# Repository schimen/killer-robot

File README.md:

# Killer robot

This repository contains all code and circuit for the robot **Rupert**, competing in [RoboWars](https://omegav.no/robotkrig) at [Omega Verksted](https://omegav.no/).

More information about Rupert and his history can be found in [history.md](./history.md).

## Projects

This repository consists of differenct projects that have different tasks in controlling the robot.
The different projects are:
- [Robot brain](./firmware/rupert-brain/): Firmware running on Rupert, receives commands and controls motors.
- [Robot pcb](./robot-pcb/): Printed circuit board supposed to control the robot. The robot brain runs on this hardware.
- [Robot control center](./control-center/): Python GUI program that controls the robot via commands.
- [Transmitter](./firmware/transmitter): Firmware for command transmitter, communicating with the control center via USB and the robot via radio.
This transmitter is deprecated, all communication with Rupert uses BLE via the "Robot control center".

## Zephyr guide

The firmware for Rupert is mainly developed in [Zephyr RTOS](https://www.zephyrproject.org/) and the SDK for Zephyr must be installed to build and upload firmware to the robot and the transmitter.
Zephyr is well documented and the latest documentation can be found [here](https://docs.zephyrproject.org/latest/index.html).

To install and get started with Zephyr, please follow [this guide](https://docs.zephyrproject.org/latest/develop/getting_started/index.html).
To install Zephyr in this project, make sure west and other dependencies from the guide is installed, and run `west update` from this repositories root folder. This will download Zephyr and relevant modules.
After installing and becoming familiar with the framework, you can install dependencies used by our hardware:
- Install ESP32 dependencies with `west espressif install`. Alternatively, follow [this guide](https://www.zephyrproject.org/zephyr-rtos-on-esp32/).

The Rupert firmware can now for example be built by the command `west build -b rupert_pcb firmware/rupert-brain` and then flashed with the command `west flash`.

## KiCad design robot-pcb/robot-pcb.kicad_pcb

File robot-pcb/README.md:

# Robot PCB

This is the PCB that controls Rupert.
It consists of a ESP32 microcontroller that communicates over bluetooth.
Motors are controlled via motor-driver and via pwm outputs.

Schematic:

PCB 3d render:

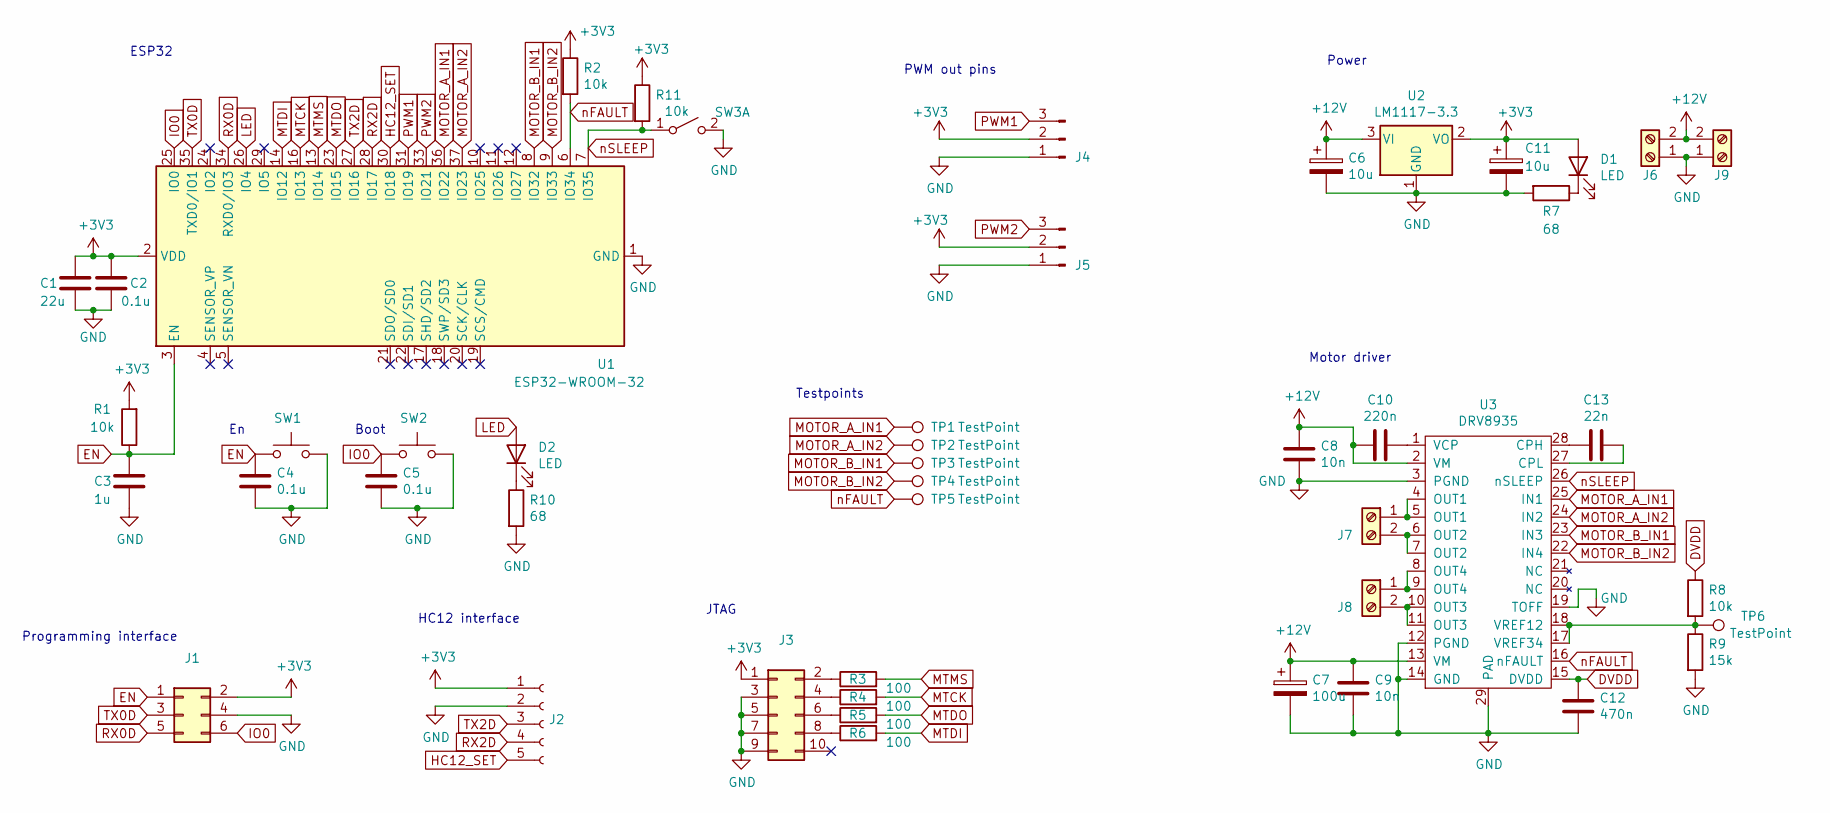
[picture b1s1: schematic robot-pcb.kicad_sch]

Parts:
C1: 22u; C_0603_1608Metric_Pad1.08x0.95mm_HandSolder
C2, C4, C5: 0.1u; C_0603_1608Metric_Pad1.08x0.95mm_HandSolder
C3: 1u; C_0603_1608Metric_Pad1.08x0.95mm_HandSolder
C6, C11: 10u; C_1206_3216Metric_Pad1.33x1.80mm_HandSolder
C7: 100u; CP_Elec_6.3x7.7
C8, C9: 10n; C_0603_1608Metric_Pad1.08x0.95mm_HandSolder
C10: 220n; C_0603_1608Metric_Pad1.08x0.95mm_HandSolder
C12: 470n; C_0603_1608Metric_Pad1.08x0.95mm_HandSolder
C13: 22n; C_0603_1608Metric_Pad1.08x0.95mm_HandSolder
D1, D2: LED; LED_0603_1608Metric_Pad1.05x0.95mm_HandSolder
J1: Conn_02x03_Odd_Even; PinHeader_2x03_P1.27mm_Vertical_SMD
J2: Conn_01x05_Female; PinSocket_1x05_P2.54mm_Vertical
J3: Conn_02x05_Odd_Even; PinHeader_2x05_P1.27mm_Vertical_SMD
J4, J5: Conn_01x03_Male; PinSocket_1x03_P2.54mm_Vertical
J6, J7, J8, J9: Screw_Terminal_01x02; TerminalBlock_bornier-2_P5.08mm
R1, R2, R8, R11: 10k; R_0603_1608Metric_Pad0.98x0.95mm_HandSolder
R3, R4, R5, R6: 100; R_0603_1608Metric_Pad0.98x0.95mm_HandSolder
R7, R10: 68; R_0603_1608Metric_Pad0.98x0.95mm_HandSolder
R9: 15k; R_0603_1608Metric_Pad0.98x0.95mm_HandSolder
SW1, SW2: SW_Push; wurth_tactile_sw
SW3: SW_DPST_x2; PinHeader_1x02_P2.54mm_Vertical
TP1, TP2, TP3, TP4, TP5, TP6: TestPoint; TestPoint_Keystone_5000-5004_Miniature
U1: ESP32-WROOM-32
U2: LM1117-3.3; SOT-223
U3: DRV8935; HTSSOP-28-1EP_4.4x9.7mm_P0.65mm_EP2.85x5.4mm

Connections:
+3V3: C1.1, C2.1, C11.1, D1.2 (A), J1.2, J2.1, J3.1, J4.2, J5.2, R1.2, R2.1, R11.1, U1.2 (VDD), U2.2 (VO), U2.4
+12V: C6.1, C7.1, C8.1, C9.1, C10.2, J6.2, J9.2, U2.3 (VI), U3.2 (VM), U3.13 (VM)
DVDD: C12.1, R8.1, U3.15 (DVDD)
EN: C3.1, C4.1, J1.1, R1.1, SW1.2, U1.3 (EN)
GND: C1.2, C2.2, C3.2, C4.2, C5.2, C6.2, C7.2, C8.2, C9.2, C11.2, C12.2, J1.4, J2.2, J3.3, J3.5, J3.7, J3.9, J4.1, J5.1, J6.1, J9.1, R7.2, R9.2, R10.2, SW1.1, SW2.2, SW3.2 (B), U1.1 (GND), U1.15 (GND), U1.38 (GND), U1.39 (GND), U2.1 (GND), U3.3 (PGND), U3.12 (PGND), U3.14 (GND), U3.19 (TOFF), U3.29 (PAD)
HC12_SET: J2.5, U1.30 (IO18)
IO0: C5.1, J1.6, SW2.1, U1.25 (IO0)
LED: D2.2 (A), U1.26 (IO4)
MOTOR_A_IN1: TP1.1, U1.36 (IO22), U3.25 (IN1)
MOTOR_A_IN2: TP2.1, U1.37 (IO23), U3.24 (IN2)
MOTOR_B_IN1: TP3.1, U1.8 (IO32), U3.23 (IN3)
MOTOR_B_IN2: TP4.1, U1.9 (IO33), U3.22 (IN4)
MTCK: R4.2, U1.16 (IO13)
MTDI: R6.2, U1.14 (IO12)
MTDO: R5.2, U1.23 (IO15)
MTMS: R3.2, U1.13 (IO14)
unnamed: C10.1, U3.1 (VCP)
unnamed: C13.1, U3.27 (CPL)
unnamed: C13.2, U3.28 (CPH)
unnamed: D1.1 (K), R7.1
unnamed: D2.1 (K), R10.1
unnamed: J3.2, R3.1
unnamed: J3.4, R4.1
unnamed: J3.6, R5.1
unnamed: J3.8, R6.1
unnamed: J7.1, U3.4 (OUT1), U3.5 (OUT1)
unnamed: J7.2, U3.6 (OUT2), U3.7 (OUT2)
unnamed: J8.1, U3.8 (OUT4), U3.9 (OUT4)
unnamed: J8.2, U3.10 (OUT3), U3.11 (OUT3)
unnamed: R8.2, R9.1, TP6.1, U3.17 (VREF34), U3.18 (VREF12)
PWM1: J4.3, U1.31 (IO19)
PWM2: J5.3, U1.33 (IO21)
RX0D: J1.5, U1.34 (RXD0/IO3)
RX2D: J2.4, U1.28 (IO17)
TX0D: J1.3, U1.35 (TXD0/IO1)
TX2D: J2.3, U1.27 (IO16)
nFAULT: R2.2, TP5.1, U1.6 (IO34), U3.16 (nFAULT)
nSLEEP: R11.2, SW3.1 (A), U1.7 (IO35), U3.26 (nSLEEP)

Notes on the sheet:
PWM out pins
ESP32
Motor driver
JTAG
HC12 interface
Power
Testpoints
Boot
Programming interface

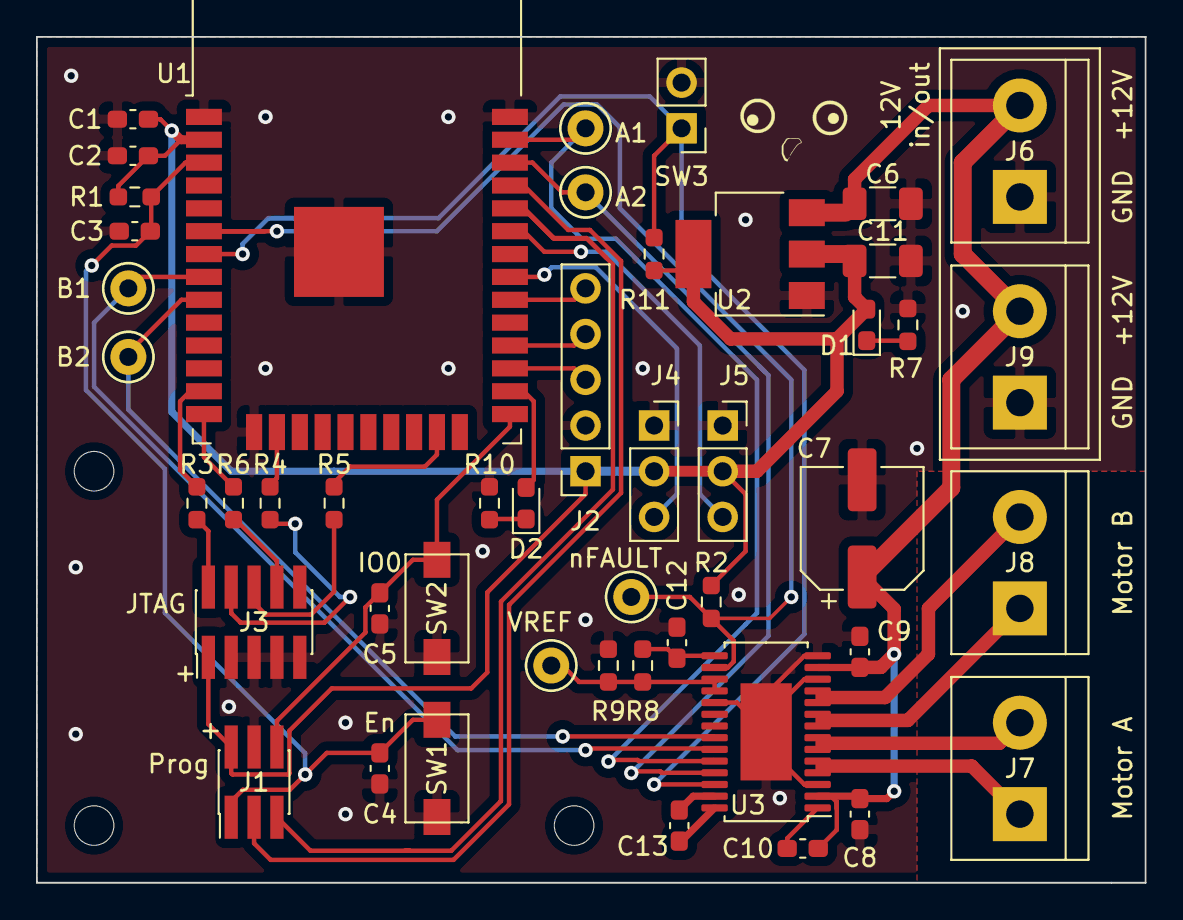
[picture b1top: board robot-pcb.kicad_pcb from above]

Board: 2 copper layers, 61.6 x 47.0 mm, 47 parts (0 on the bottom side), 38 nets.

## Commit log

2021-10-28 robot-brain: Motor control testing
2021-10-28 robot-brain: Added README
2021-10-29 changed everything
2021-10-29 killer-robot: Added functionality for backup radio module
2021-10-29 backup-transmitter: added 433MHz support
2021-10-29 flaut
2021-10-29 fikset opp koblingsskjema
2021-10-30 robot-control-center: included nix shell declaration
2021-10-30 robot-control-panel: created control panel for controlling robot
2021-10-31 robot-control-panel: fixed entry focus issue and limited motor values
2021-11-03 backup-transmitter: complete remake of the backup transmitter
2021-11-03 robot-brain/Motor.h: "fixed" bug when nSteps is 0
2021-11-03 robot-brain: Added servo and got backup radio working
2021-11-03 transmitter: Changed name from backup transmitter
2021-11-03 transmitter: added readme
2021-11-04 robot-bran: stopped "clearing" buffer and some other receiver stuff
2021-11-04 Motor: now it makes sure the end speed matches the desired speed
2021-11-05 minor updates
2021-11-05 control-panel: added alternate speed, transmitter choice and windows support
2021-11-05 Control panel: added reverse mode
2021-11-05 control panel: fixed reverse function
2021-11-05 control panel: cleaned up with functions, added more serial control and many new comments
2022-03-03 Final tweaks before contest
2022-04-10 Remove arduino transmitter sketch
2022-04-10 Add transmitter circuit
2022-04-21 Add zephyr transmitter
2022-04-21 Add gitignore
2022-04-21 Make control panel interface with new transmitter
2022-04-21 Update control panel to send motor commands correctly
2022-04-23 last minute stressed changes to make weapon work :)
2022-09-17 Add ble interface and rearrange interface drivers
2022-09-17 Add more to gitignore
2022-09-17 Add pcb for esp32
2022-09-19 Remove power switch from pcb
2022-09-26 Finish pcb v1.0
2022-09-26 Use fhs for espressif sdk
2022-09-26 Add command_writer and remove unnecessary functions and comments
2022-09-26 Add requests
2022-09-26 Renamed drivers to command lib
2022-09-30 Update transmitter to new command lib
2022-10-01 Add esp32 overlay
2022-10-01 Update command_lib for use with transmitter
2022-10-01 Add pwm to config
2022-10-01 Add shell.nix to gitignore
2022-10-01 Remove shell.nix
2022-10-01 Ignore more files
2022-10-02 Add individual kconfig for gatt and uart
2022-10-02 Add esp32 to transmitter boards
2022-10-02 Fix bugs in esp32 overlay
2022-10-02 Move arduino backups
2022-10-03 Add send-command to gatt
2022-10-03 Update ble tests
2022-10-03 Start testing with motors
2022-10-03 Fix notification print
2022-10-03 Fix pwm bug in motor lib
2022-10-11 Blink led in workthread
2022-10-11 Fix pwm issues in motor.c
2022-10-22 Major refactor of control panel
    - Add bluetooth
    - Add module for all communication
    - Register atexit functions
    - Update serial implementation
2022-10-22 Update bleak test programs
2022-10-22 Remove busy status and fix bt disconnect callback bug
2022-10-22 Receive multiple commands and remove unused permissions
2022-10-22 Remove peripheral duplicate
2022-10-22 Update name bt device in robot brain
2022-10-24 Update bluetooth name in tests
2022-10-24 Implement acceleration with threads for motors
2022-10-24 Minor edits
2022-10-25 Minor format change
2022-10-25 Check for too high pulse in pwm
2022-10-25 Clang format
2022-10-29 Add interrupt support for nsleep and add uart for commands
2022-10-29 Add uart commands in prj.conf
2022-10-29 Bad fix for pwm problem
2022-10-29 Adjust baudrate and print incoming commands in background
2022-10-30 Add send_command func to header
2022-10-30 Update robot-brain esp32 dts
2022-10-30 Update transmitter overlays and minor tweaks in main
2022-11-01 Add basic readme for control-panel
2022-11-02 Request connection parameters on connection
2022-11-02 Small updates to pwm in overlay
2022-11-04 Add weapon command and other updates to control-panel
2022-11-04 Show time used for each command
2022-11-05 Add logging and other smaller updates
2022-11-05 Update esp32 overlay
2022-11-05 Fix disconnected callback and print ping time bt
2022-11-06 Add log messages to command.c
2022-11-06 Add enable and disable functions to command-libs
2022-11-06 Add motor and weapon off functions
2022-11-06 Move massage handler to thread and implement sleep mode
2022-11-06 Intergate weapon to gui
2022-11-08 Start with pwm chanel 0 and use 9600 for radio
2022-11-08 Add custom interval and step form motors
2022-11-08 Tune stack sizes
2022-11-08 Use new command start and end and init state pin high
2022-11-08 Update transmitter overlays and config
2022-11-09 Use new start and end command
2022-11-09 Add logging and other minor updates
2022-11-09 Fix port listing bug
2022-11-09 Init state pin logic low
2022-11-09 Turn off weapon pwm at 127
2022-11-09 Increase number of threads
2022-11-09 Set logging level 0
2022-11-09 Do all sleep stuff in workthread
2022-11-09 Fix update value function
2022-11-10 Add stuff to gitignore
2022-11-10 Show bluetooth ping at control-panel
2022-11-10 Major refactor for communication classes - Class for each interface - General interface sendcommand structure - Routinely ping all active interfaces and print result
2022-11-12 Don't reverse weapon
2022-11-16 Add pictures and some description to README
2022-11-16 Make images bigger
2022-12-12 Bluetooth and control-panel fixes
    - Implement write-without response in gatt_command
    - Implement proper notifications
    - Use actual mtu in bleak
    - Other smaller fixes
2022-12-13 Use different pwm channels to fix buggy pwm
2023-04-15 Add timeout when receiving commands
2023-04-15 Print RSSI when connecting to bt
2023-04-15 Remove Arduino backup
2023-04-15 Add some documentation for pcb
2023-04-15 Rename pcb-render image
2023-04-15 Move python bluetooth tests and add to ignore to gitignore
2023-04-15 Resize images in pcb readme
2023-04-15 Add 3d models folder
2023-04-22 Use reverse weapon again
2023-05-19 Update robot pcb holder and update kicad version
2023-05-19 Add some print statements to scan program
2023-07-02 Add test drivers (not yet working)
2023-07-02 Rearrange firmware structure
2023-07-03 Apply refactor to driver code and make able to build
2023-07-03 Add spi library to header file
2023-07-03 Add alias and test code for motion-sensor
2023-07-03 Add rupert_pcb board
2023-07-03 Fix sensor driver log-level and device initialization
2023-08-24 Add non-working sensor implementation
2023-08-25 Refer to correct spi device and support float print
2023-08-25 Mostly format changes
2023-08-27 Fix sensor reading bug and use max scale reading
2023-08-27 Remove HC12 interface from rupert-brain
2023-08-27 Add debug service for raw sensor values
2023-08-29 Add magnetometer
2023-08-29 Add captain ruper to Readme
2023-08-30 Add some more delay for magnetometer
2023-08-30 Rewrite sensor test
2023-08-30 Use little endian for magnetometer
2023-08-30 Rewrite sensor data plotting program for reuse
2023-09-12 Add live plot function
2023-10-03 Add spinner test model
2023-10-07 Remove FCStd1 files
2023-10-10 Add spinner model v2
2023-10-14 Add timer to debug server notification
2023-10-17 Use new motor configuration and rework motor library for bl motor
2023-11-05 Slight change in bl pulse values
2023-11-05 Go back to dc motors and remove motion sensor for robowars
2023-11-05 Add rupert h2023 and some more info to readme
2023-11-05 Fomat changes to readme
2025-02-11 Update KiCad version
2025-02-11 Add separate markdown document for rupert history
2025-02-11 Add note for deprecated transmitter in readme
2025-02-11 Add chassis v3 model
2025-02-14 SPlit up spinner model to multiple projects
